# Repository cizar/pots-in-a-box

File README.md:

# POTS in a box

Una central telefónica analógica de 2 líneas para que computadoras retro con módem se
llamen entre sí, sin una línea telefónica real. La red analógica (POTS, *Plain Old
Telephone Service*) ya no existe: esta caja la simula entera.

```
 [Commodore 64 + Modem 1200] ──RJ11── ┌──────────────┐ ──RJ11── [PC con BBS + módem]
                                      │ POTS in a box │
                                      └──────┬───────┘
                                          12 V
```

- Alimentación de línea, tono de invitación a marcar, ring, tono de llamada y de ocupado.
- Marcado por tonos (DTMF) y por pulsos. Cualquier número marcado hace sonar la otra línea.
- Tonos de Argentina (ITU-T E.180) o de EE.UU., con una llave física.
- Se alimenta con una fuente externa de 12 V: no hay 220 V dentro de la caja.
- ATmega328P, un MT8870 por línea y ULN2003A. Todos los componentes son pasantes.

## Estado

- **Firmware:** completo y probado en la PC (`make -C firmware test`). Todavía no se probó en
  hardware.
- **Hardware:** en prueba de banco ([docs/prueba-banco.md](docs/prueba-banco.md)). Primer
  esquemático completo en KiCad, con verificación eléctrica sin errores; el PCB viene después
  de la prueba de banco.

## Documentación

- [Diseño](docs/superpowers/specs/2026-11-13-pots-2-lineas-design.md)
- [Firmware: cómo compilar y grabar, mapa de pines](firmware/README.md)
- [Prueba de banco](docs/prueba-banco.md)
- [Hardware: esquemático en KiCad](hardware/README.md)

## Seguridad

Las líneas llevan hasta 48 V de continua y la ring, con corriente limitada. Leé la sección
de seguridad de la prueba de banco antes de armar nada.

## Licencia

Firmware bajo GPL-3.0-or-later; hardware y documentación bajo CERN-OHL-S-2.0. Ver
[LICENSE.md](LICENSE.md).

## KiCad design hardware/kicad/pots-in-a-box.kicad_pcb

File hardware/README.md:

# Hardware de POTS in a box

Proyecto KiCad 10 en `hardware/kicad/`. Se abre con `pots-in-a-box.kicad_pro`.

## Cómo está armado

El esquemático **se genera con un script**, no se dibuja a mano:

```sh
python3 hardware/tools/gen_schematic.py
```

El script (`hardware/tools/gen_schematic.py`) tiene la lista de componentes y la red de cada
pata, bloque por bloque, y una función de dibujo por hoja que ubica los componentes y une las
patas con cables, puntos de unión y rieles de alimentación, como un esquemático hecho a mano.
Se usan etiquetas solo donde un cable tendría que cruzar otros (las E/S del ATmega, los
contactos del relé de ring, las salidas del MT8870) o para ir a otra hoja.

Al terminar, el script exporta la netlist con `kicad-cli` y la **compara con la lista de
redes del script**: si un cable quedó mal dibujado (un componente girado al revés, una unión
de más o de menos), lo informa como problema. Tiene que decir `netlist check: OK`. **Si se
edita el `.kicad_sch` a mano y después se vuelve a correr el script, los cambios se pierden**:
los cambios de circuito van en el script.

El script tampoco toca `pots-in-a-box.kicad_pro` si ya existe, porque ahí están las clases de
red y las reglas de DRC.

Al final, el script también genera la **lista de materiales** con `hardware/tools/gen_bom.py`.
Ese script se puede correr solo y necesita `kicad-cli` y Google Chrome. Escribe dos archivos:

- `hardware/bom.csv`, con los datos del esquemático;
- `hardware/bom.pdf`, para imprimir: A4, agrupado por tipo, con casillas para tildar y lo que no
  está en el esquemático (zócalos, módulo elevador, fuente, gabinete).

Las descripciones de encapsulado, las notas y los extras están en tablas al principio de
`gen_bom.py`. Si aparece una huella nueva sin descripción, el PDF muestra el nombre crudo de la
huella.

**Hasta cuándo:** el script es la fuente hasta tener los resultados de la prueba de banco.
Antes de diseñar el PCB se congela: desde ese momento los `.kicad_sch` pasan a ser la fuente,
se editan solo en KiCad y el script queda como histórico.

Verificación eléctrica (ERC), desde la raíz del repo:

```sh
/Applications/KiCad/KiCad.app/Contents/MacOS/kicad-cli sch erc --severity-all hardware/kicad/pots-in-a-box.kicad_sch
```

## Hojas

| Hoja | Contenido |
|---|---|
| `pots-in-a-box` (raíz) | los bloques y las conexiones entre ellos |
| `power` | jack de 12 V, PTC, diodo de protección, 7805, conector del módulo elevador (`V_LINE`), resistencia de descarga, LED de encendido |
| `mcu` | ATmega328P (mapa de pines de `firmware/README.md`, compatible con Arduino Uno), cristal, ISP, conector serie estilo FTDI, llave AR/US, LED de llamada |
| `ring` | puente H compartido: 2 × IR2104 + 4 × IRF540N, R_BRIDGE, inversor BC547 |
| `link` | ULN2003A y relé de unión de audio L1–L2 |
| `line` (×2: `line_L1`, `line_L2`) | bloque de línea completo: RJ11, TVS, limitador de corriente, relé de ring DPDT, PC817, acople por capacitor, protección del audio, filtro de tono, MT8870 |

La hoja `line` es el bloque que se repite: para más líneas se agregan instancias.
Referencias: L1 usa la serie 100 (R101, U102…) y L2 la serie 200.

## Decisiones de esta versión

- **Puente H con IR2104** (driver de medio puente de 600 V con tiempo muerto interno) y 4
  MOSFET de canal N, en lugar del puente con MOSFET de canal P de la prueba de banco.
  La pata ~SD de cada IR2104 va directo a +12 V (la entrada admite hasta VCC), sin
  resistencia de pull-up: los drivers quedan siempre habilitados.
- **Elevador como módulo:** `J2` es una bornera para el módulo elevador. El elevador propio
  (por ejemplo MC34063 + MOSFET) se diseña con los resultados de la prueba de banco.
- **Un cristal por MT8870.** Compartir uno queda para cuando se confirme en la prueba.
- **Partes del panel por conector:** la llave AR/US va por un conector de 2 pines; los LEDs
  de encendido y de llamada están en la placa, a reubicar según la caja.
- **Jack de 12 V:** pata 1 = centro (+). Verificar contra el jack que se compre.

## PCB preliminar (para elegir el gabinete)

`hardware/kicad/pots-in-a-box.kicad_pcb` es una **ubicación inicial, sin rutear**, generada
desde el esquemático:

```sh
/Applications/KiCad/KiCad.app/Contents/Frameworks/Python.framework/Versions/Current/bin/python3 hardware/tools/gen_pcb.py
```

Sirve para definir el tamaño de la placa, dónde van los conectores y qué altura tienen los
componentes, para elegir o diseñar el gabinete. No sirve para fabricar.

- **Diseño en mil** (milésimas de pulgada, la grilla de los DIP). Cada pieza se ubica por su
  origen (la pata 1), así que DIP y resistencias quedan con todas las patas sobre la grilla de
  100 mil. Las filas de piezas iguales van cada 200 mil. Las piezas de paso métrico (cerámicos
  de 5 mm, el capacitor de 15 mm, cristales, fusibles) tienen la pata 1 en la grilla y la otra
  donde cae. Las piezas ubicadas automáticamente van a una grilla de 50 mil.
- Placa de 5500 × 3850 mil (139,70 × 97,79 mm), 2 capas, 4 agujeros M3 a 150 mil de cada borde.
  Gabinete previsto: ABS de 150 × 120 × 40 mm, admite hasta 5500 × 3850 mil. La placa ya tiene
  ese tamaño; faltan las muescas de los tubos de cierre y los agujeros sobre los soportes,
  cuando estén las medidas. Mientras se acomoda a mano, el script genera la placa igual aunque
  haya piezas fuera del borde o superpuestas, y las lista para corregirlas en KiCad.
- **Organización modular.** Mirando el panel trasero desde atrás, de izquierda a derecha:
  jack de 12 V y bloques compartidos, línea L1, línea L2. Cada línea es una columna de 1400 mil (35,56 mm)
  que va de atrás hacia adelante, con las mismas piezas en el mismo lugar (los RJ11 quedan
  separados 1400 mil). Para agregar una línea se suma una columna en ese extremo (`LINES`,
  `LINE_W` en el script).
- **Panel trasero** (coordenadas vistas desde arriba, x = 0 en el extremo de L2): RJ11 L2
  (x = 600 mil), RJ11 L1 (x = 2000 mil), jack de 12 V (x = 5000 mil).
- **Panel frontal:** LED PWR y LED CALL (posiciones provisorias, se están acomodando a
  mano). El conector de la llave AR/US (SW1) va adentro de la placa, con cable al panel.
- **Columna de línea** (ubicada a mano en `LINE_LAYOUT`, de atrás hacia adelante siguiendo la
  señal): RJ11 con el TVS pegado a sus patas y el relé de ring al lado; alimentación del lazo
  (F, Q101/Q102 junto a R101/R102); capacitor de acople; optoacoplador con su diodo; red de
  audio y filtro de tono; MT8870 acostado con su cristal en OSC y su desacople en VDD; abajo
  de Q1–Q4, las resistencias serie paradas.
- **Bus DTMF:** las salidas Q1–Q4 de todos los MT8870 van, cada una por su resistencia de
  1 k, a un bus común (`DTMF_Q1..Q4`) que entra al ATmega por PC2–PC5. Se deja libre una
  franja de 300 mil a lo largo del frente de las columnas para ese bus y para las señales propias
  de cada línea (TONE, StD, OFFHOOK, relé). El ATmega está girado para que PC2–PC5 queden
  sobre esa franja.
- Bloques compartidos: puente H (ring) atrás, junto a L1; alimentación atrás, en el extremo;
  MCU adelante junto a L1 (con su cristal en XTAL1/2, `SHARED_LAYOUT`); relé de unión y
  ULN2003A adelante, en el extremo.
- No hay espacio reservado para el elevador propio: por ahora queda como módulo externo en `J2`,
  que el script ubica donde haya lugar en la zona compartida.
- La biblioteca de KiCad no tiene modelo 3D del RJ12: `hardware/kicad/3d/rj12_body.wrl` es una
  caja de las medidas del conector, solo para el render.
- Ver en 3D: abrir el PCB en KiCad y usar Ver → Visor 3D (Alt+3).

**Mover piezas a mano y pasarlas al script.** Se puede ajustar la ubicación en KiCad
(mover, rotar) y después copiarla al script, para no perderla al regenerar:

```sh
/Applications/KiCad/KiCad.app/Contents/Frameworks/Python.framework/Versions/Current/bin/python3 hardware/tools/pull_layout.py
```

Compara el PCB guardado con uno recién generado y escribe en `gen_pcb.py` cada pieza que se
movió: las de línea (de L1 o de L2) en `LINE_LAYOUT`, que vale para todas las líneas;
las compartidas en `SHARED_LAYOUT`. Si se acomodó una sola línea, `--line L2` (o `L1`) toma
las posiciones solo de esa y las copia a las demás; `--dry-run` muestra los cambios sin escribir.
Las posiciones se miden desde el borde de la placa, así que no importa si KiCad la movió en la hoja.
Conviene mover las piezas con la grilla de KiCad en 25 o 50 mil (el script deja la placa dentro del marco
de la hoja, con la esquina en 1000,1000 mil, y pone ahí el origen de la grilla); si alguna queda fuera, el script lo avisa. Los conectores del panel y los agujeros solo los informa
(van en `EDGE_PARTS`). Las pistas se ignoran. Hay que correrlo sobre un PCB generado por la
versión actual del script.

**Clases de red** (en `kicad/pots-in-a-box.kicad_pro`, no en el PCB; `gen_pcb.py` conserva ese archivo al
regenerar, porque guardar el PCB desde Python lo reescribiría con valores por defecto):

| Clase | Redes | Pista | Separación |
|---|---|---|---|
| `HV` | V_LINE, RING_A/B, riel del puente (`Net-(Q3-D)`), lado alto de los IR2104 (VB, HO, gate alta), TIP/RING de cada jack, alimentación del lazo (Q1x1), TIP_FEED, RING_RET | 0,5 mm | 0,6 mm |
| `Power` | +12V, +5V, GND | 0,6 mm | 0,2 mm |
| `Default` | el resto | 0,25 mm | 0,2 mm |

La separación de `HV` sale de IPC-2221 para capa externa sin recubrir hasta 150 V (V_LINE de
24–48 V para la línea, hasta ~90 V para el ring). Varias redes `HV` no tienen nombre en el
esquemático y se asignan por patrón (`Net-(D?02-A?)`, `Net-(Q?01-?)`, …): si cambian las
referencias, hay que revisar los patrones. `kicad/pots-in-a-box.kicad_dru` deja las patas de un
mismo transistor de la alimentación del lazo (TO-126 / TO-92) con la separación normal, porque el
encapsulado las tiene más juntas que 0,6 mm.
Q1x2 (BC546) usa el TO-92 de patas separadas (`TO-92_Inline_Wide`, 2,54 mm): con el TO-92
común no entra una pista `HV` entre sus patas. El script deja además una franja de 1 mm
(`EDGE_KEEPOUT`) sin pistas ni vías a lo largo del borde, porque Freerouting no respeta la
distancia al borde. El ancho mínimo de pista de la placa es 0,15 mm: Freerouting angosta las
pistas al 75 % al entrar a las patas.

**Ruteo de prueba:** Tools → External Plugins → Freerouting (plugin instalado desde el
Plugin and Content Manager). Sirve para ver si la ubicación se puede rutear; el ruteo se pierde
al regenerar.

Cuando se congele el esquemático, el PCB también pasa a editarse en KiCad: la ubicación final y
el ruteo se hacen a mano y este script queda como histórico.

## Pendiente

- [ ] Valores finales de `V_LINE`, R_SENSE, acople y nivel de tono (salen de la prueba de banco).
- [ ] Huella alternativa del transformador 600:600 en paralelo con el capacitor de acople (spec §7.4).
- [ ] Elevador propio en la placa, en lugar del módulo.
- [x] Dibujo con cables en todas las hojas.
- [x] PCB preliminar sin rutear, para el gabinete.
- [ ] PCB: separar la zona de alta tensión (`V_LINE`, puente, relés, RJ11) de la lógica.

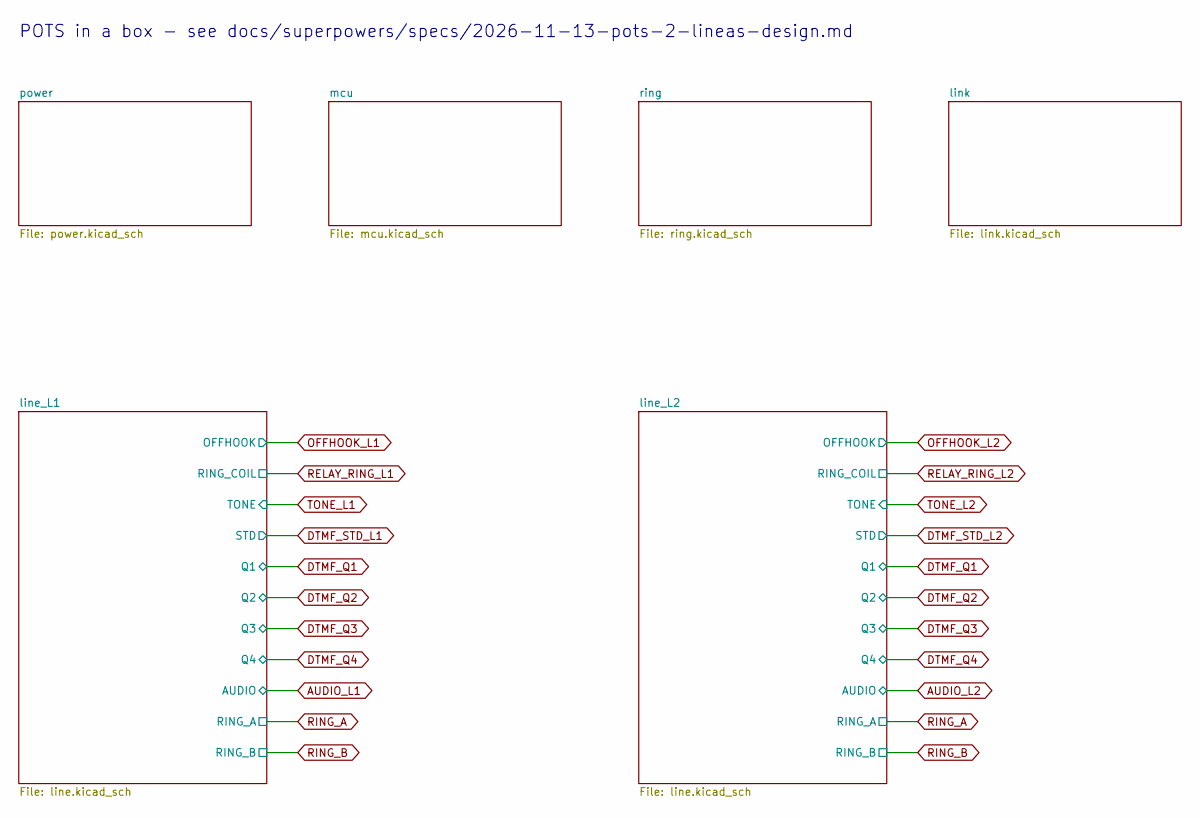
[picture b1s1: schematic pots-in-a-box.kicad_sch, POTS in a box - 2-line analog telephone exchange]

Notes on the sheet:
POTS in a box - see docs/superpowers/specs/2026-11-13-pots-2-lineas-design.md

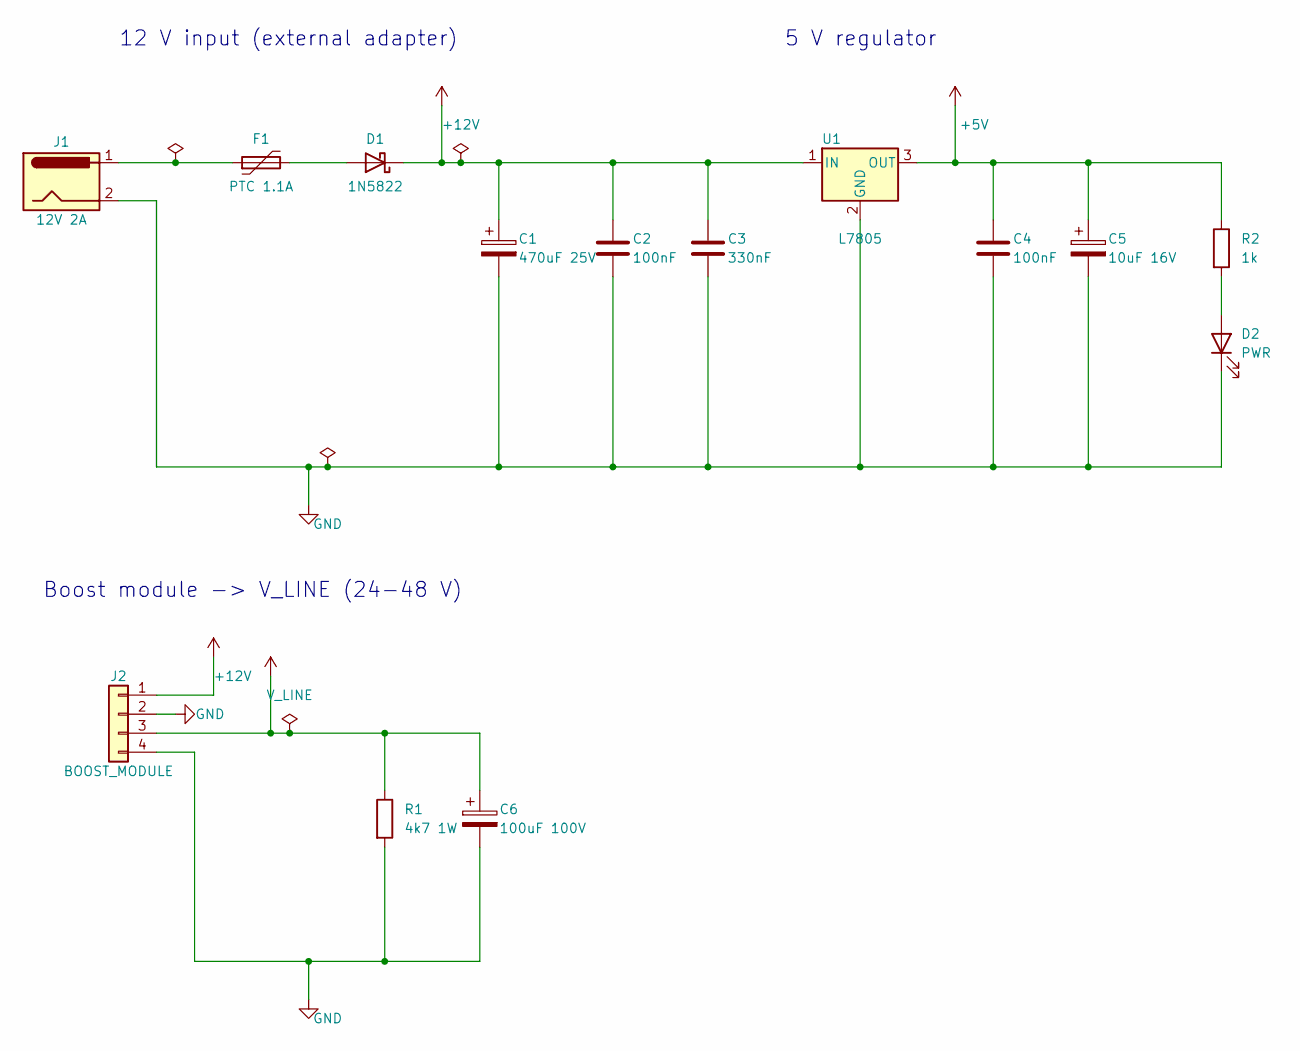
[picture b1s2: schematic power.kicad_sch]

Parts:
C1: 470uF 25V; CP_Radial_D10.0mm_P5.00mm
C2, C4: 100nF; C_Disc_D5.0mm_W2.5mm_P5.00mm
C3: 330nF; C_Disc_D5.0mm_W2.5mm_P5.00mm
C5: 10uF 16V; CP_Radial_D8.0mm_P3.50mm
C6: 100uF 100V; CP_Radial_D10.0mm_P5.00mm
D1: 1N5822; D_DO-41_SOD81_P10.16mm_Horizontal
D2: PWR; LED_D3.0mm
F1: PTC 1.1A; Fuse_Bourns_MF-RG300
J1: 12V 2A; BarrelJack_Horizontal
J2: BOOST_MODULE; TerminalBlock_Phoenix_MKDS-1,5-4-5.08_1x04_P5.08mm_Horizont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
R1: 4k7 1W; R_Axial_DIN0414_L11.9mm_D4.5mm_P15.24mm_Horizontal
R2: 1k; R_Axial_DIN0207_L6.3mm_D2.5mm_P10.16mm_Horizontal
U1: L7805; TO-220-3_Vertical

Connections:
+5V: C4.1, C5.1, R2.1, U1.3 (OUT); also elsewhere on the board
unnamed: D1.2 (A), F1.2
unnamed: D2.2 (A), R2.2

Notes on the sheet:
12 V input (external adapter)
5 V regulator
Boost module -> V_LINE (24-48 V)

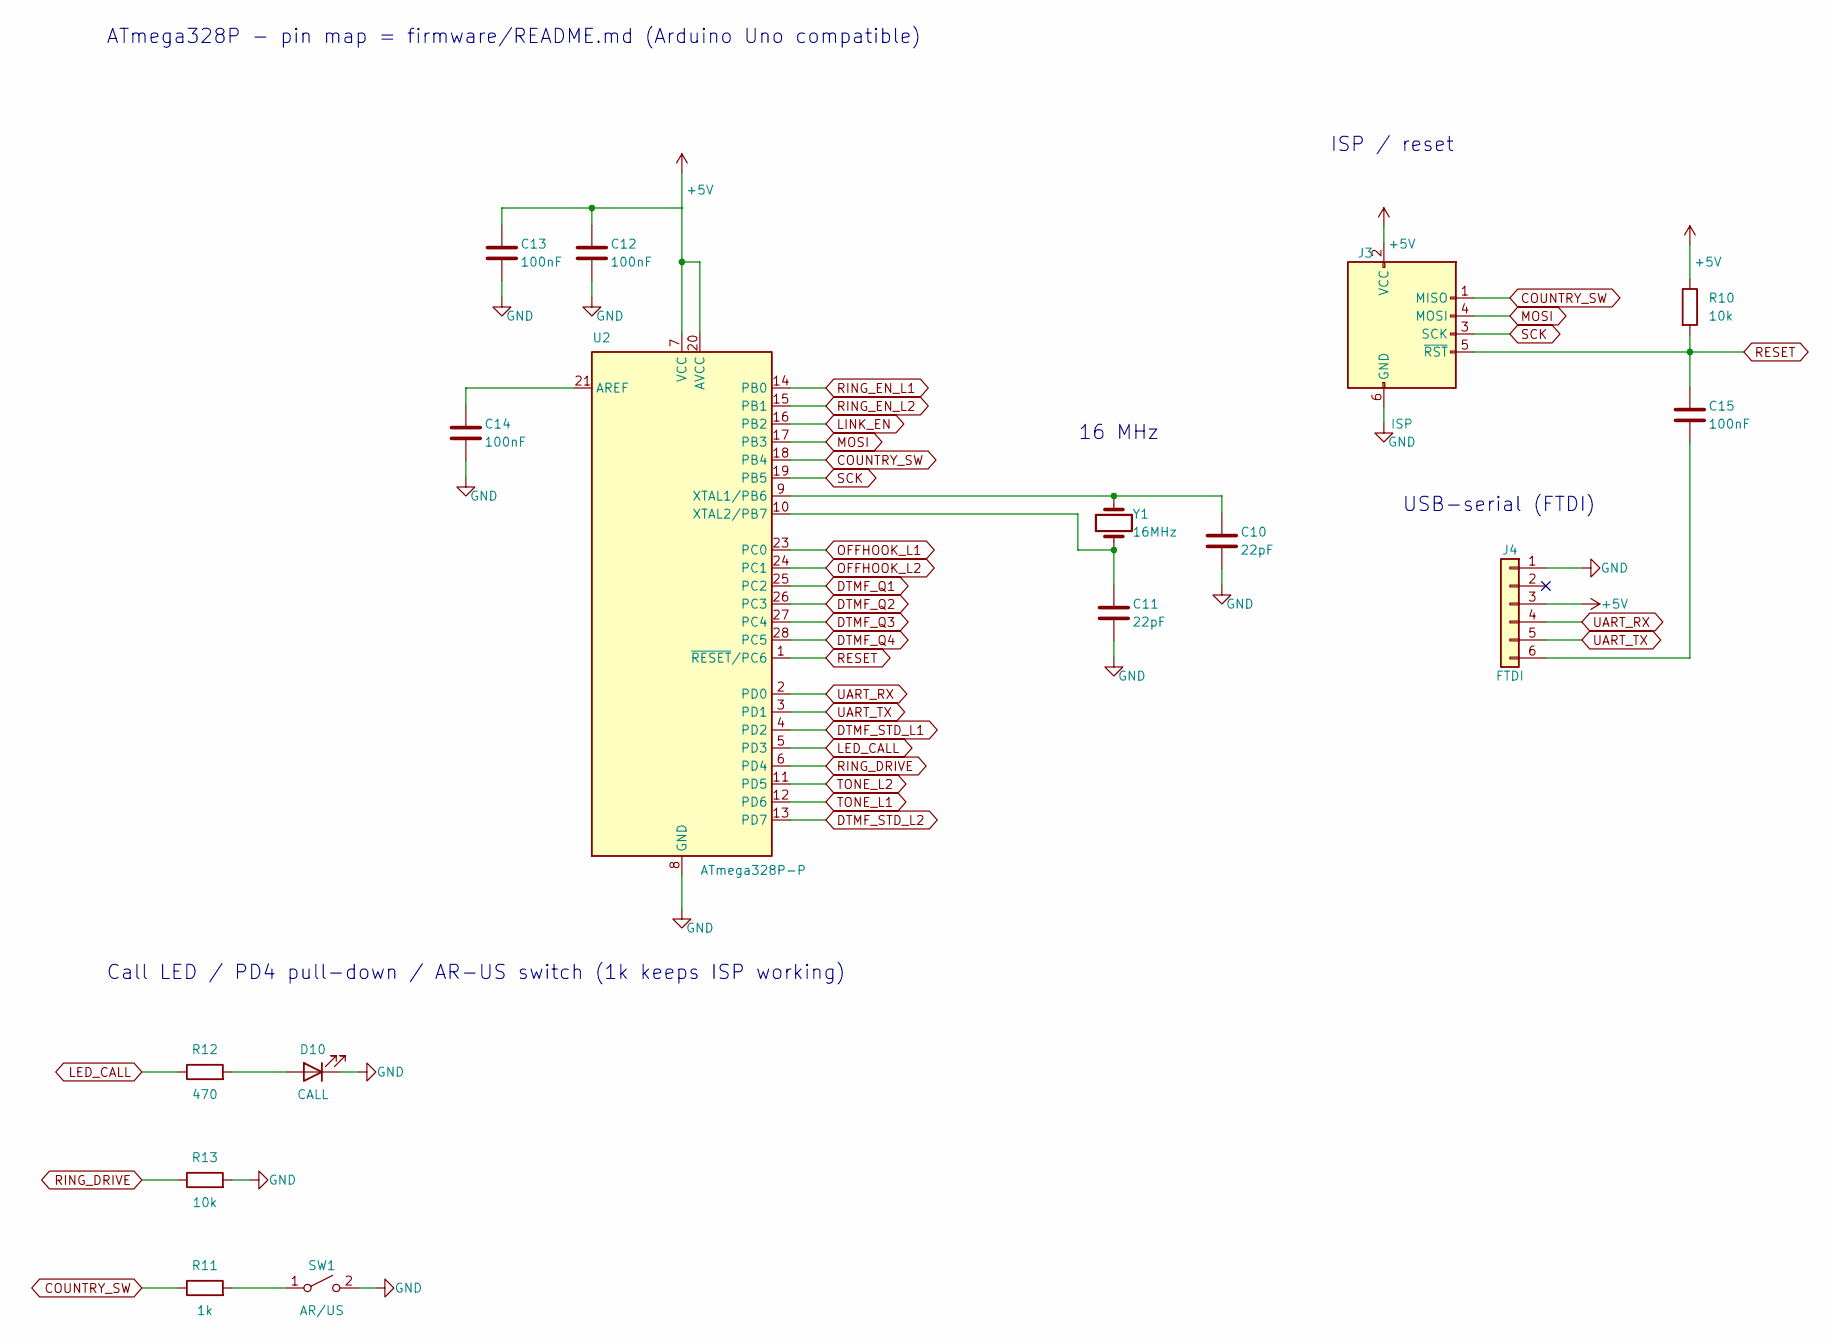
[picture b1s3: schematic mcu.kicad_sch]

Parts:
C10, C11: 22pF; C_Disc_D5.0mm_W2.5mm_P5.00mm
C12, C13, C14, C15: 100nF; C_Disc_D5.0mm_W2.5mm_P5.00mm
D10: CALL; LED_D3.0mm
J3: ISP; IDC-Header_2x03_P2.54mm_Vertical
J4: FTDI; PinHeader_1x06_P2.54mm_Vertical
R10, R13: 10k; R_Axial_DIN0207_L6.3mm_D2.5mm_P10.16mm_Horizontal
R11: 1k; R_Axial_DIN0207_L6.3mm_D2.5mm_P10.16mm_Horizontal
R12: 470; R_Axial_DIN0207_L6.3mm_D2.5mm_P10.16mm_Horizontal
SW1: AR/US; PinHeader_1x02_P2.54mm_Vertical
U2: ATmega328P-P; DIP-28_W7.62mm_Socket
Y1: 16MHz; Crystal_HC49-4H_Vertical

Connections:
+5V: C12.1, C13.1, J3.2 (VCC), J4.3, R10.1, U2.7 (VCC), U2.20 (AVCC); also elsewhere on the board
COUNTRY_SW: J3.1 (MISO), R11.1, U2.18 (PB4)
DTMF_Q1: U2.25 (PC2); also elsewhere on the board
DTMF_Q2: U2.26 (PC3); also elsewhere on the board
DTMF_Q3: U2.27 (PC4); also elsewhere on the board
DTMF_Q4: U2.28 (PC5); also elsewhere on the board
DTMF_STD_L1: U2.4 (PD2); also elsewhere on the board
DTMF_STD_L2: U2.13 (PD7); also elsewhere on the board
LED_CALL: R12.1, U2.5 (PD3)
LINK_EN: U2.16 (PB2); also elsewhere on the board
MOSI: J3.4 (MOSI), U2.17 (PB3)
unnamed: D10.2 (A), R12.2
unnamed: C15.1, J4.6
unnamed: R11.2, SW1.1 (A)
unnamed: C14.1, U2.21 (AREF)
unnamed: C10.1, U2.9 (XTAL1/PB6), Y1.1
unnamed: C11.1, U2.10 (XTAL2/PB7), Y1.2
OFFHOOK_L1: U2.23 (PC0); also elsewhere on the board
OFFHOOK_L2: U2.24 (PC1); also elsewhere on the board
RESET: C15.2, J3.5 (~RST), R10.2, U2.1 (~RESET/PC6)
RING_DRIVE: R13.1, U2.6 (PD4); also elsewhere on the board
RING_EN_L1: U2.14 (PB0); also elsewhere on the board
RING_EN_L2: U2.15 (PB1); also elsewhere on the board
SCK: J3.3 (SCK), U2.19 (PB5)
TONE_L1: U2.12 (PD6); also elsewhere on the board
TONE_L2: U2.11 (PD5); also elsewhere on the board
UART_RX: J4.4, U2.2 (PD0)
UART_TX: J4.5, U2.3 (PD1)

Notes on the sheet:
ATmega328P - pin map = firmware/README.md (Arduino Uno compatible)
16 MHz
ISP / reset
USB-serial (FTDI)
Call LED / PD4 pull-down / AR-US switch (1k keeps ISP working)

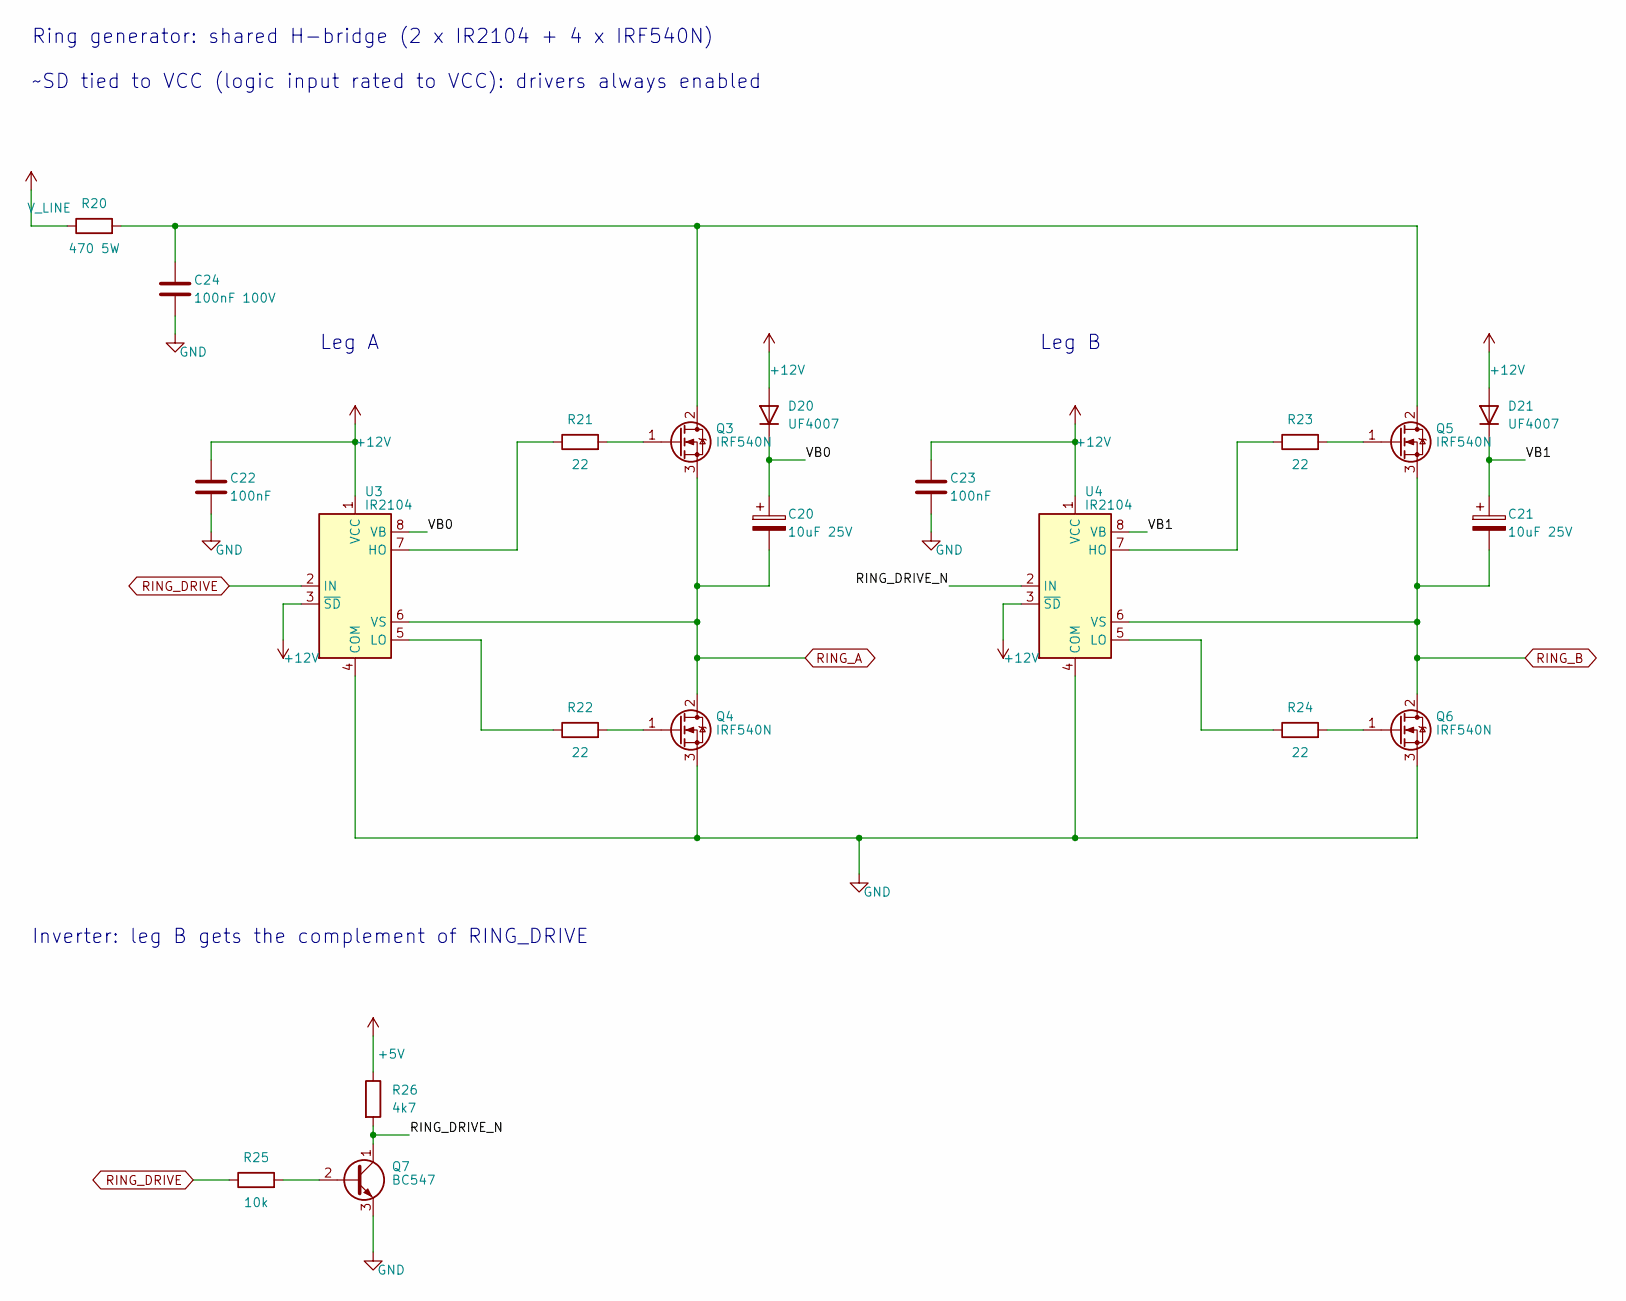
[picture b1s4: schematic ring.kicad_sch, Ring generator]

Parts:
C20, C21: 10uF 25V; CP_Radial_D8.0mm_P3.50mm
C22, C23: 100nF; C_Disc_D5.0mm_W2.5mm_P5.00mm
C24: 100nF 100V; C_Disc_D5.0mm_W2.5mm_P5.00mm
D20, D21: UF4007; D_DO-41_SOD81_P10.16mm_Horizontal
Q3, Q4, Q5, Q6: IRF540N; TO-220-3_Vertical
Q7: BC547; TO-92_Inline
R20: 470 5W; R_Axial_Power_L25.0mm_W6.4mm_P27.94mm
R21, R22, R23, R24: 22; R_Axial_DIN0207_L6.3mm_D2.5mm_P10.16mm_Horizontal
R25: 10k; R_Axial_DIN0207_L6.3mm_D2.5mm_P10.16mm_Horizontal
R26: 4k7; R_Axial_DIN0207_L6.3mm_D2.5mm_P10.16mm_Horizontal
U3, U4: IR2104; DIP-8_W7.62mm

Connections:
+5V: R26.1; also elsewhere on the board
/ring/RING_DRIVE_N: Q7.1 (C), R26.2, U4.2 (IN)
/ring/VB0: C20.1, D20.1 (K), U3.8 (VB)
/ring/VB1: C21.1, D21.1 (K), U4.8 (VB)
unnamed: C24.1, Q3.2 (D), Q5.2 (D), R20.2
unnamed: Q3.1 (G), R21.2
unnamed: Q4.1 (G), R22.2
unnamed: Q5.1 (G), R23.2
unnamed: Q6.1 (G), R24.2
unnamed: Q7.2 (B), R25.2
unnamed: R21.1, U3.7 (HO)
unnamed: R22.1, U3.5 (LO)
unnamed: R23.1, U4.7 (HO)
unnamed: R24.1, U4.5 (LO)
RING_A: C20.2, Q3.3 (S), Q4.2 (D), U3.6 (VS); also elsewhere on the board
RING_B: C21.2, Q5.3 (S), Q6.2 (D), U4.6 (VS); also elsewhere on the board
RING_DRIVE: R25.1, U3.2 (IN); also elsewhere on the board

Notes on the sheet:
Ring generator: shared H-bridge (2 x IR2104 + 4 x IRF540N)
~SD tied to VCC (logic input rated to VCC): drivers always enabled
Leg A
Leg B
Inverter: leg B gets the complement of RING_DRIVE

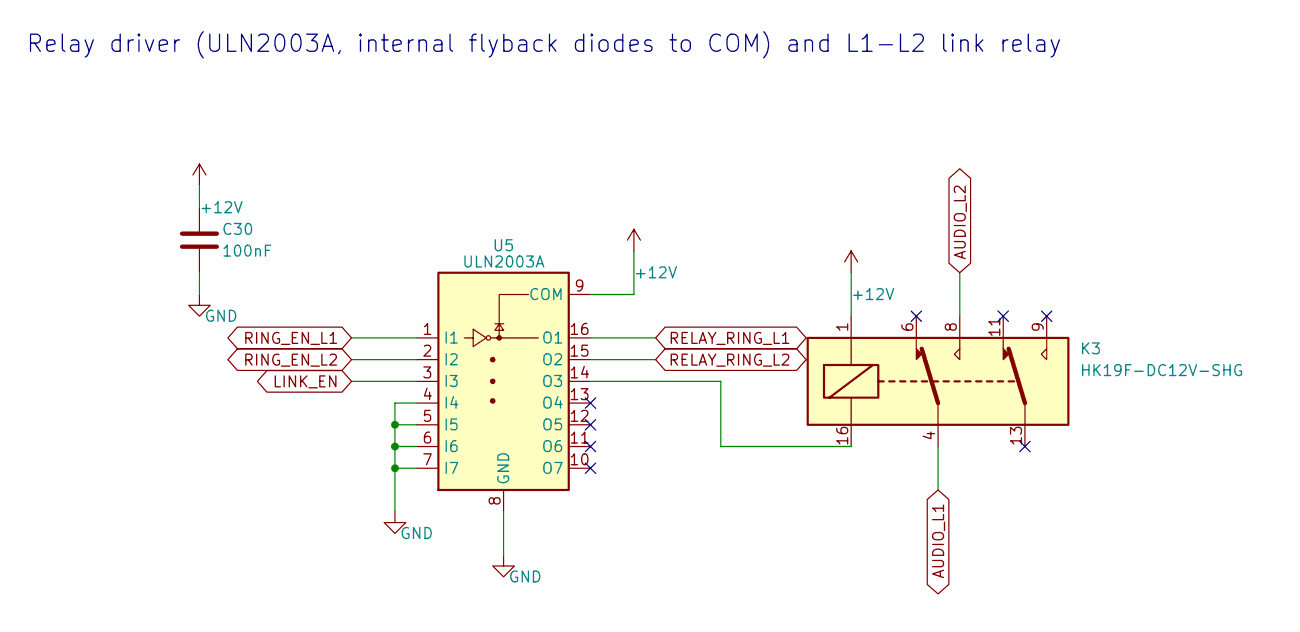
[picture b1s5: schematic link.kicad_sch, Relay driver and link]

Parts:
C30: 100nF; C_Disc_D5.0mm_W2.5mm_P5.00mm
K3: HK19F-DC12V-SHG; Relay_DPDT_Omron_G5V-2
U5: ULN2003A; DIP-16_W7.62mm

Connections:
AUDIO_L1: K3.4; also elsewhere on the board
AUDIO_L2: K3.8; also elsewhere on the board
LINK_EN: U5.3 (I3); also elsewhere on the board
unnamed: K3.16, U5.14 (O3)
RELAY_RING_L1: U5.16 (O1); also elsewhere on the board
RELAY_RING_L2: U5.15 (O2); also elsewhere on the board
RING_EN_L1: U5.1 (I1); also elsewhere on the board
RING_EN_L2: U5.2 (I2); also elsewhere on the board

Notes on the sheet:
Relay driver (ULN2003A, internal flyback diodes to COM) and L1-L2 link relay

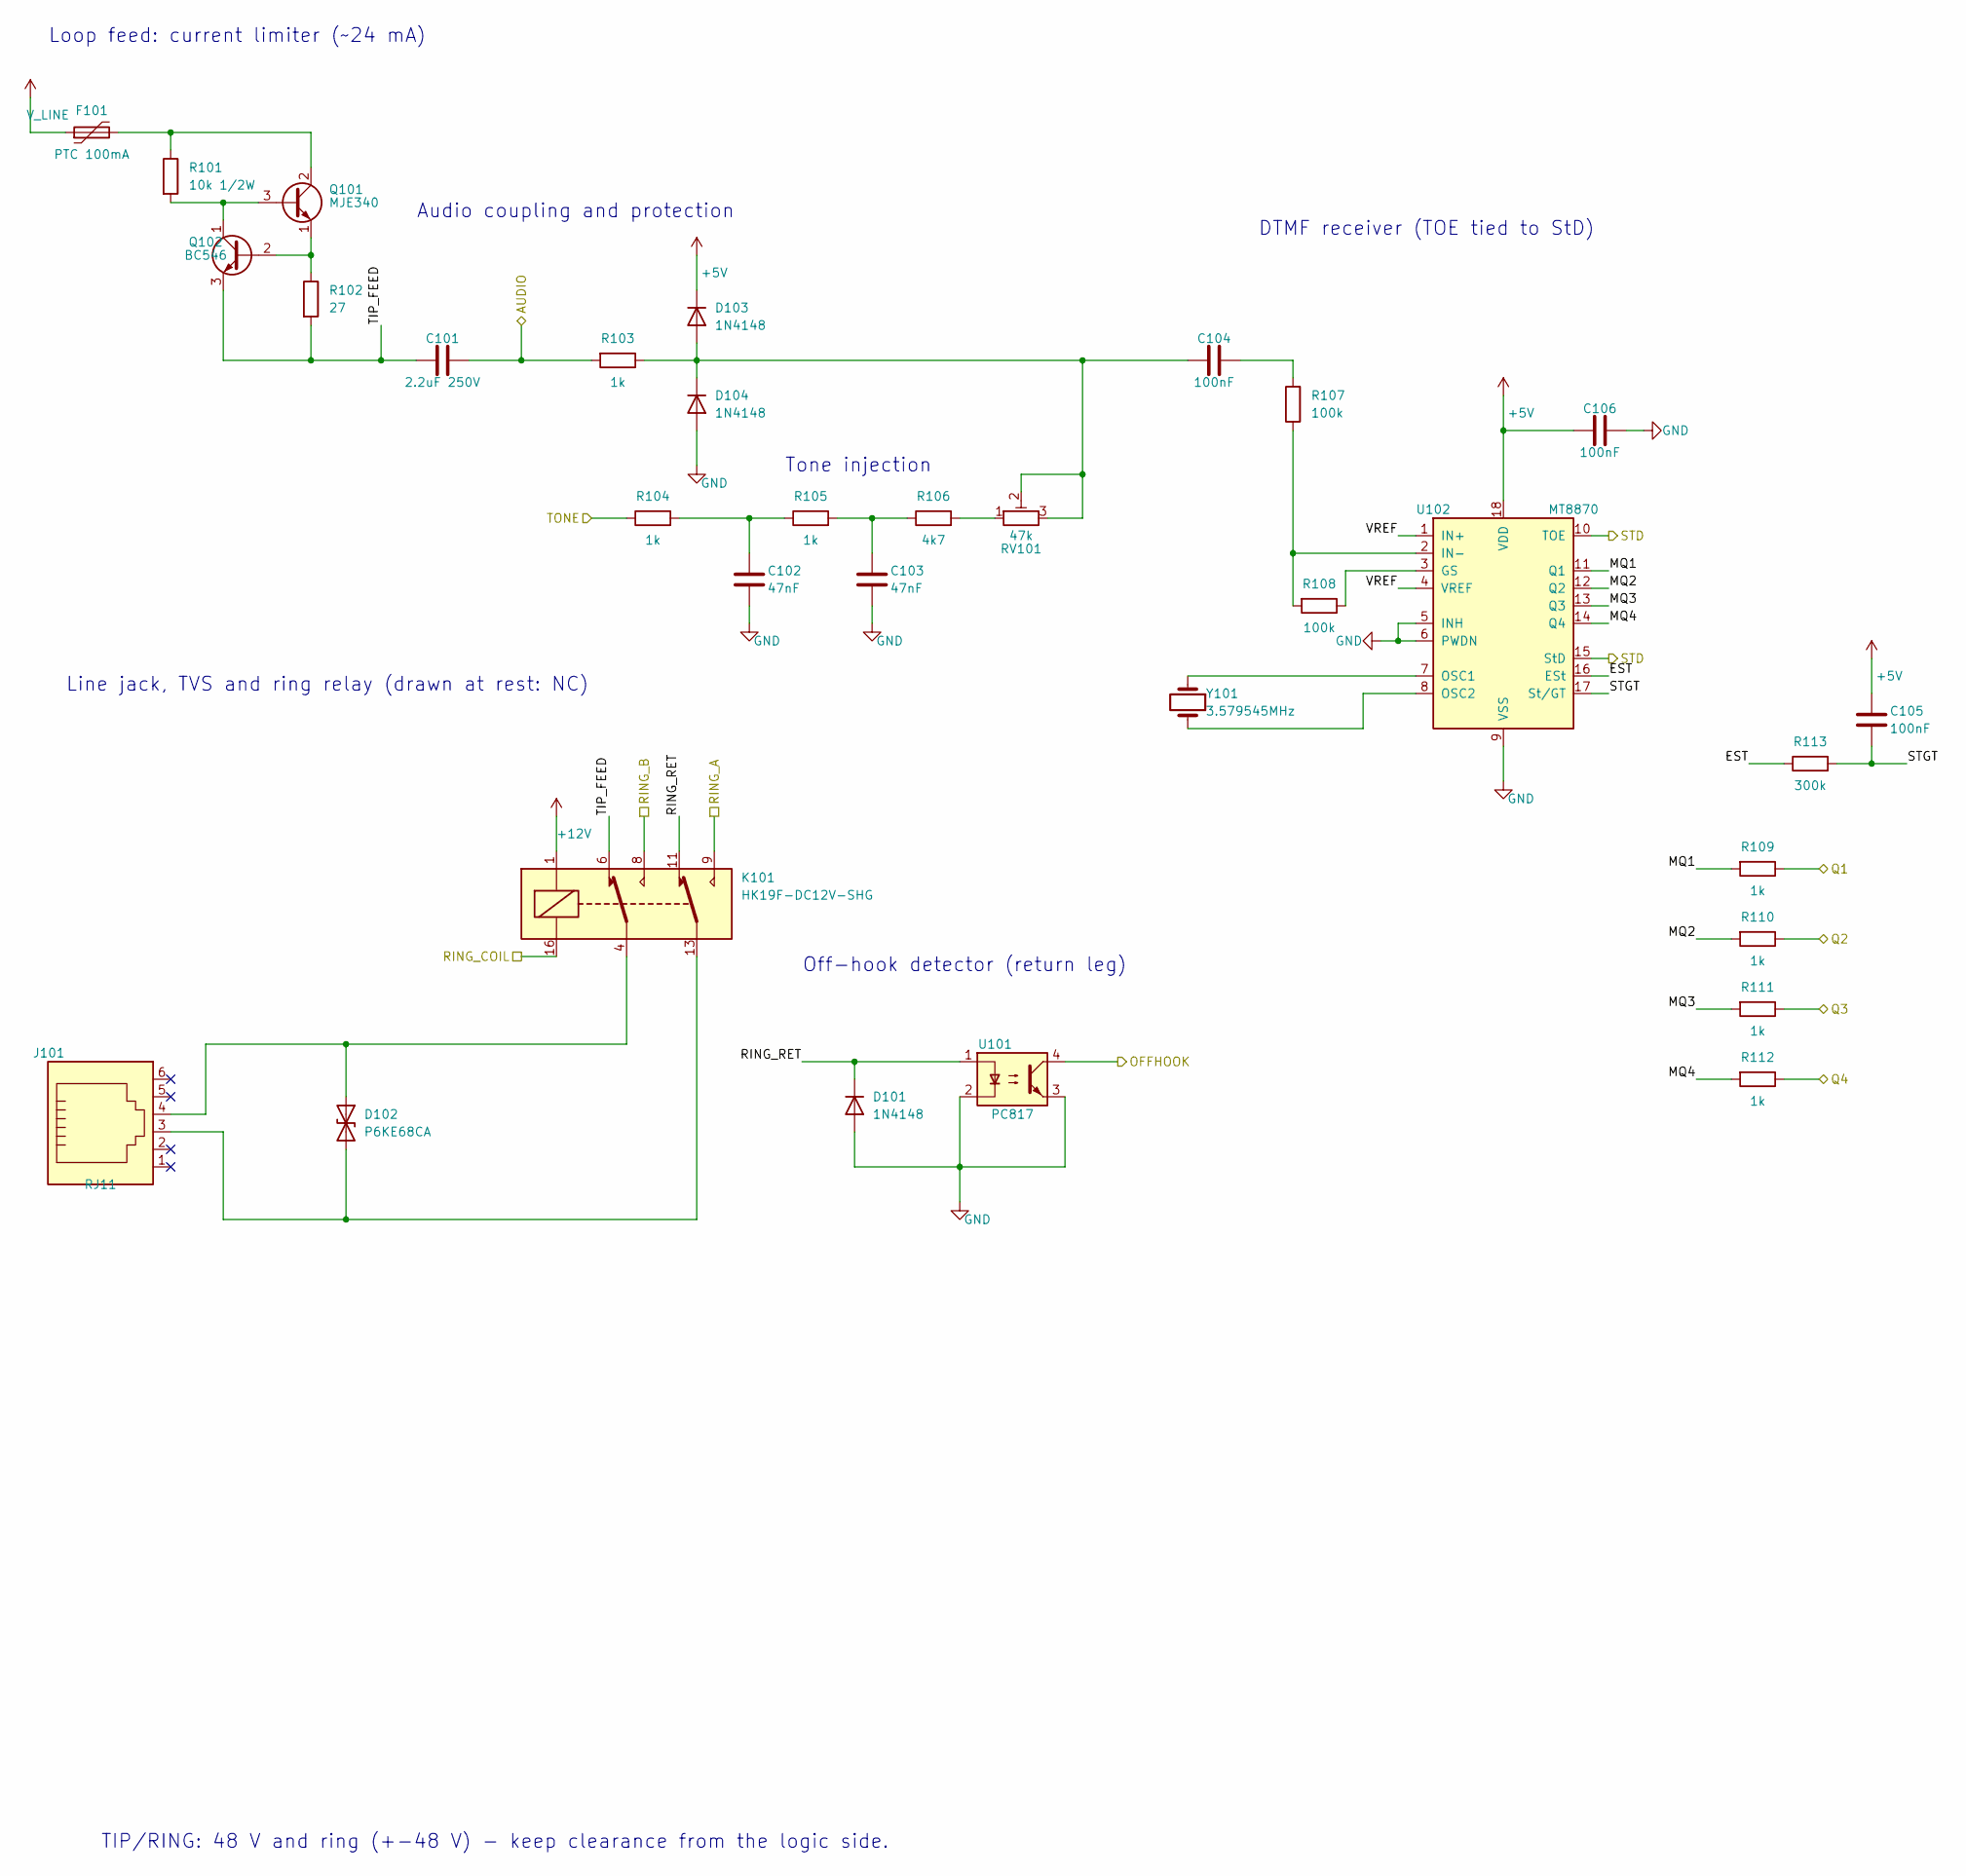
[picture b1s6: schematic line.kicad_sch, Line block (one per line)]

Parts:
C101: 2.2uF 250V; C_Rect_L18.0mm_W8.0mm_P15.00mm_FKS3_FKP3
C102, C103: 47nF; C_Disc_D5.0mm_W2.5mm_P5.00mm
C104, C105, C106: 100nF; C_Disc_D5.0mm_W2.5mm_P5.00mm
D101, D103, D104: 1N4148; D_DO-35_SOD27_P7.62mm_Horizontal
D102: P6KE68CA; D_DO-15_P10.16mm_Horizontal
F101: PTC 100mA; Fuse_Bourns_MF-RG300
J101: RJ11; RJ12_Amphenol_54601-x06_Horizontal
K101: HK19F-DC12V-SHG; Relay_DPDT_Omron_G5V-2
Q101: MJE340; TO-126-3_Vertical
Q102: BC546; TO-92_Inline_Wide
R101: 10k 1/2W; R_Axial_DIN0309_L9.0mm_D3.2mm_P12.70mm_Horizontal
R102: 27; R_Axial_DIN0207_L6.3mm_D2.5mm_P10.16mm_Horizontal
R103, R104, R105, R109, R110, R111, R112: 1k; R_Axial_DIN0207_L6.3mm_D2.5mm_P10.16mm_Horizontal
R106: 4k7; R_Axial_DIN0207_L6.3mm_D2.5mm_P10.16mm_Horizontal
R107, R108: 100k; R_Axial_DIN0207_L6.3mm_D2.5mm_P10.16mm_Horizontal
R113: 300k; R_Axial_DIN0207_L6.3mm_D2.5mm_P10.16mm_Horizontal
RV101: 47k; Potentiometer_Bourns_3296W_Vertical
U101: PC817; DIP-4_W7.62mm
U102: MT8870; DIP-18_W7.62mm
Y101: 3.579545MHz; Crystal_HC49-4H_Vertical

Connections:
+5V: C105.1, C106.1, D103.1 (K), U102.18 (VDD); also elsewhere on the board
/line_L1/EST: R113.1, U102.16 (ESt)
/line_L1/MQ1: R109.2, U102.11 (Q1)
/line_L1/MQ2: R110.2, U102.12 (Q2)
/line_L1/MQ3: R111.2, U102.13 (Q3)
/line_L1/MQ4: R112.2, U102.14 (Q4)
/line_L1/RING_RET: D101.1 (K), K101.11, U101.1
/line_L1/STGT: C105.2, R113.2, U102.17 (St/GT)
/line_L1/TIP_FEED: C101.1, K101.6, Q102.3 (E), R102.2
/line_L1/VREF: U102.1 (IN+), U102.4 (VREF)
AUDIO_L1: C101.2, R103.2; also elsewhere on the board
DTMF_Q1: R109.1; also elsewhere on the board
DTMF_Q2: R110.1; also elsewhere on the board
DTMF_Q3: R111.1; also elsewhere on the board
DTMF_Q4: R112.1; also elsewhere on the board
DTMF_STD_L1: U102.10 (TOE), U102.15 (StD); also elsewhere on the board
unnamed: C102.1, R104.2, R105.1
unnamed: C103.1, R105.2, R106.1
unnamed: C104.2, R107.2
unnamed: D102.1 (A1), J101.4, K101.4
unnamed: D102.2 (A2), J101.3, K101.13
unnamed: C104.1, D103.2 (A), D104.1 (K), R103.1, RV101.2, RV101.3
unnamed: Q101.3 (B), Q102.1 (C), R101.2
unnamed: F101.2, Q101.2 (C), R101.1
unnamed: Q101.1 (E), Q102.2 (B), R102.1
unnamed: R106.2, RV101.1
unnamed: R108.1, U102.3 (GS)
unnamed: R107.1, R108.2, U102.2 (IN-)
unnamed: U102.7 (OSC1), Y101.1
unnamed: U102.8 (OSC2), Y101.2
OFFHOOK_L1: U101.4; also elsewhere on the board
RELAY_RING_L1: K101.16; also elsewhere on the board
RING_A: K101.9; also elsewhere on the board
RING_B: K101.8; also elsewhere on the board
TONE_L1: R104.1; also elsewhere on the board

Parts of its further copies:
C201: 2.2uF 250V; C_Rect_L18.0mm_W8.0mm_P15.00mm_FKS3_FKP3
C202, C203: 47nF; C_Disc_D5.0mm_W2.5mm_P5.00mm
C204, C205, C206: 100nF; C_Disc_D5.0mm_W2.5mm_P5.00mm
D201, D203, D204: 1N4148; D_DO-35_SOD27_P7.62mm_Horizontal
D202: P6KE68CA; D_DO-15_P10.16mm_Horizontal
F201: PTC 100mA; Fuse_Bourns_MF-RG300
J201: RJ11; RJ12_Amphenol_54601-x06_Horizontal
K201: HK19F-DC12V-SHG; Relay_DPDT_Omron_G5V-2
Q201: MJE340; TO-126-3_Vertical
Q202: BC546; TO-92_Inline_Wide
R201: 10k 1/2W; R_Axial_DIN0309_L9.0mm_D3.2mm_P12.70mm_Horizontal
R202: 27; R_Axial_DIN0207_L6.3mm_D2.5mm_P10.16mm_Horizontal
R203, R204, R205, R209, R210, R211, R212: 1k; R_Axial_DIN0207_L6.3mm_D2.5mm_P10.16mm_Horizontal
R206: 4k7; R_Axial_DIN0207_L6.3mm_D2.5mm_P10.16mm_Horizontal
R207, R208: 100k; R_Axial_DIN0207_L6.3mm_D2.5mm_P10.16mm_Horizontal
R213: 300k; R_Axial_DIN0207_L6.3mm_D2.5mm_P10.16mm_Horizontal
RV201: 47k; Potentiometer_Bourns_3296W_Vertical
U201: PC817; DIP-4_W7.62mm
U202: MT8870; DIP-18_W7.62mm
Y201: 3.579545MHz; Crystal_HC49-4H_Vertical

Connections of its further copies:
+5V: C205.1, C206.1, D203.1 (K), U202.18 (VDD); also elsewhere on the board
/line_L2/EST: R213.1, U202.16 (ESt)
/line_L2/MQ1: R209.2, U202.11 (Q1)
/line_L2/MQ2: R210.2, U202.12 (Q2)
/line_L2/MQ3: R211.2, U202.13 (Q3)
/line_L2/MQ4: R212.2, U202.14 (Q4)
/line_L2/RING_RET: D201.1 (K), K201.11, U201.1
/line_L2/STGT: C205.2, R213.2, U202.17 (St/GT)
/line_L2/TIP_FEED: C201.1, K201.6, Q202.3 (E), R202.2
/line_L2/VREF: U202.1 (IN+), U202.4 (VREF)
AUDIO_L2: C201.2, R203.2; also elsewhere on the board
DTMF_Q1: R209.1; also elsewhere on the board
DTMF_Q2: R210.1; also elsewhere on the board
DTMF_Q3: R211.1; also elsewhere on the board
DTMF_Q4: R212.1; also elsewhere on the board
DTMF_STD_L2: U202.10 (TOE), U202.15 (StD); also elsewhere on the board
unnamed: C202.1, R204.2, R205.1
unnamed: C203.1, R205.2, R206.1
unnamed: C204.2, R207.2
unnamed: D202.1 (A1), J201.4, K201.4
unnamed: D202.2 (A2), J201.3, K201.13
unnamed: C204.1, D203.2 (A), D204.1 (K), R203.1, RV201.2, RV201.3
unnamed: Q201.3 (B), Q202.1 (C), R201.2
unnamed: F201.2, Q201.2 (C), R201.1
unnamed: Q201.1 (E), Q202.2 (B), R202.1
unnamed: R206.2, RV201.1
unnamed: R208.1, U202.3 (GS)
unnamed: R207.1, R208.2, U202.2 (IN-)
unnamed: U202.7 (OSC1), Y201.1
unnamed: U202.8 (OSC2), Y201.2
OFFHOOK_L2: U201.4; also elsewhere on the board
RELAY_RING_L2: K201.16; also elsewhere on the board
RING_A: K201.9; also elsewhere on the board
RING_B: K201.8; also elsewhere on the board
TONE_L2: R204.1; also elsewhere on the board

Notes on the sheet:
Loop feed: current limiter (~24 mA)
Audio coupling and protection
Tone injection
DTMF receiver (TOE tied to StD)
Line jack, TVS and ring relay (drawn at rest: NC)
Off-hook detector (return leg)
TIP/RING: 48 V and ring (+-48 V) - keep clearance from the logic side.

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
